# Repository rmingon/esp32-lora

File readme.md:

# ESP32 LoRa Nunchuck System

## Overview
This project integrates an ESP32 microcontroller with LoRa communication and two Nunchuck connectors, enabling remote control and data transmission applications. The system is designed for long-range communication while leveraging the Wii Nunchuck controllers for user input.

## Features
- **ESP32**: Wi-Fi and Bluetooth-enabled microcontroller
- **LoRa Module**: Long-range communication support
- **Dual Nunchuck Connectors on Separate I²C Buses**
- **Powered via USB**: No LiPo battery required

## Hardware Requirements
- ESP32 development board
- LoRa module (RFM95W-868S2)
- Two Wii Nunchuck controllers
- Nunchuck connectors
- USB power source
- Jumper wires & breadboard (or custom PCB)

## Wiring Diagram (Based on Schematic)
| ESP32 Pin | LoRa Pin | Nunchuck 1 Pin | Nunchuck 2 Pin |
|-----------|---------|---------------|---------------|
| 3.3V      | VCC     | VCC           | VCC           |
| GND       | GND     | GND           | GND           |
| GPIO5     | NSS     | -             | -             |
| GPIO18    | SCK     | -             | -             |
| GPIO19    | MISO    | -             | -             |
| GPIO23    | MOSI    | -             | -             |
| GPIO26    | DIO0    | -             | -             |
| GPIO21    | -       | SDA (I²C 1)   | -             |
| GPIO22    | -       | SCL (I²C 1)   | -             |
| GPIO25    | -       | -             | SDA (I²C 2)   |
| GPIO33    | -       | -             | SCL (I²C 2)   |

## Software Requirements
- Arduino IDE / PlatformIO
- ESP32 board package
- LoRa library (e.g., `RadioHead` or `LoRa.h`)
- Nunchuck library (e.g., `Wire.h`, `ArduinoNunchuk.h`)

## Usage
1. Connect the hardware components as per the wiring diagram.
2. Power up the ESP32 via USB.
3. Use the Nunchuck controllers to send data via LoRa.
4. Monitor data via serial output.

## Example Code
```cpp
#include <Wire.h>
#include <ArduinoNunchuk.h>
#include <LoRa.h>

TwoWire I2C_1 = TwoWire(0);
TwoWire I2C_2 = TwoWire(1);

ArduinoNunchuk nunchuk1;
ArduinoNunchuk nunchuk2;

void setup() {
    Serial.begin(115200);
    I2C_1.begin(21, 22); // SDA1 = GPIO21, SCL1 = GPIO22
    I2C_2.begin(25, 33); // SDA2 = GPIO25, SCL2 = GPIO33
    
    nunchuk1.init(I2C_1);
    nunchuk2.init(I2C_2);
    
    LoRa.begin(915E6);
}

void loop() {
    nunchuk1.update();
    nunchuk2.update();
    
    LoRa.beginPacket();
    LoRa.print(nunchuk1.analogX);
    LoRa.print(",");
    LoRa.print(nunchuk2.analogX);
    LoRa.endPacket();
    
    delay(100);
}
```

## Contributing
Feel free to submit issues or pull requests for improvements and bug fixes.

---
Happy coding! 🚀

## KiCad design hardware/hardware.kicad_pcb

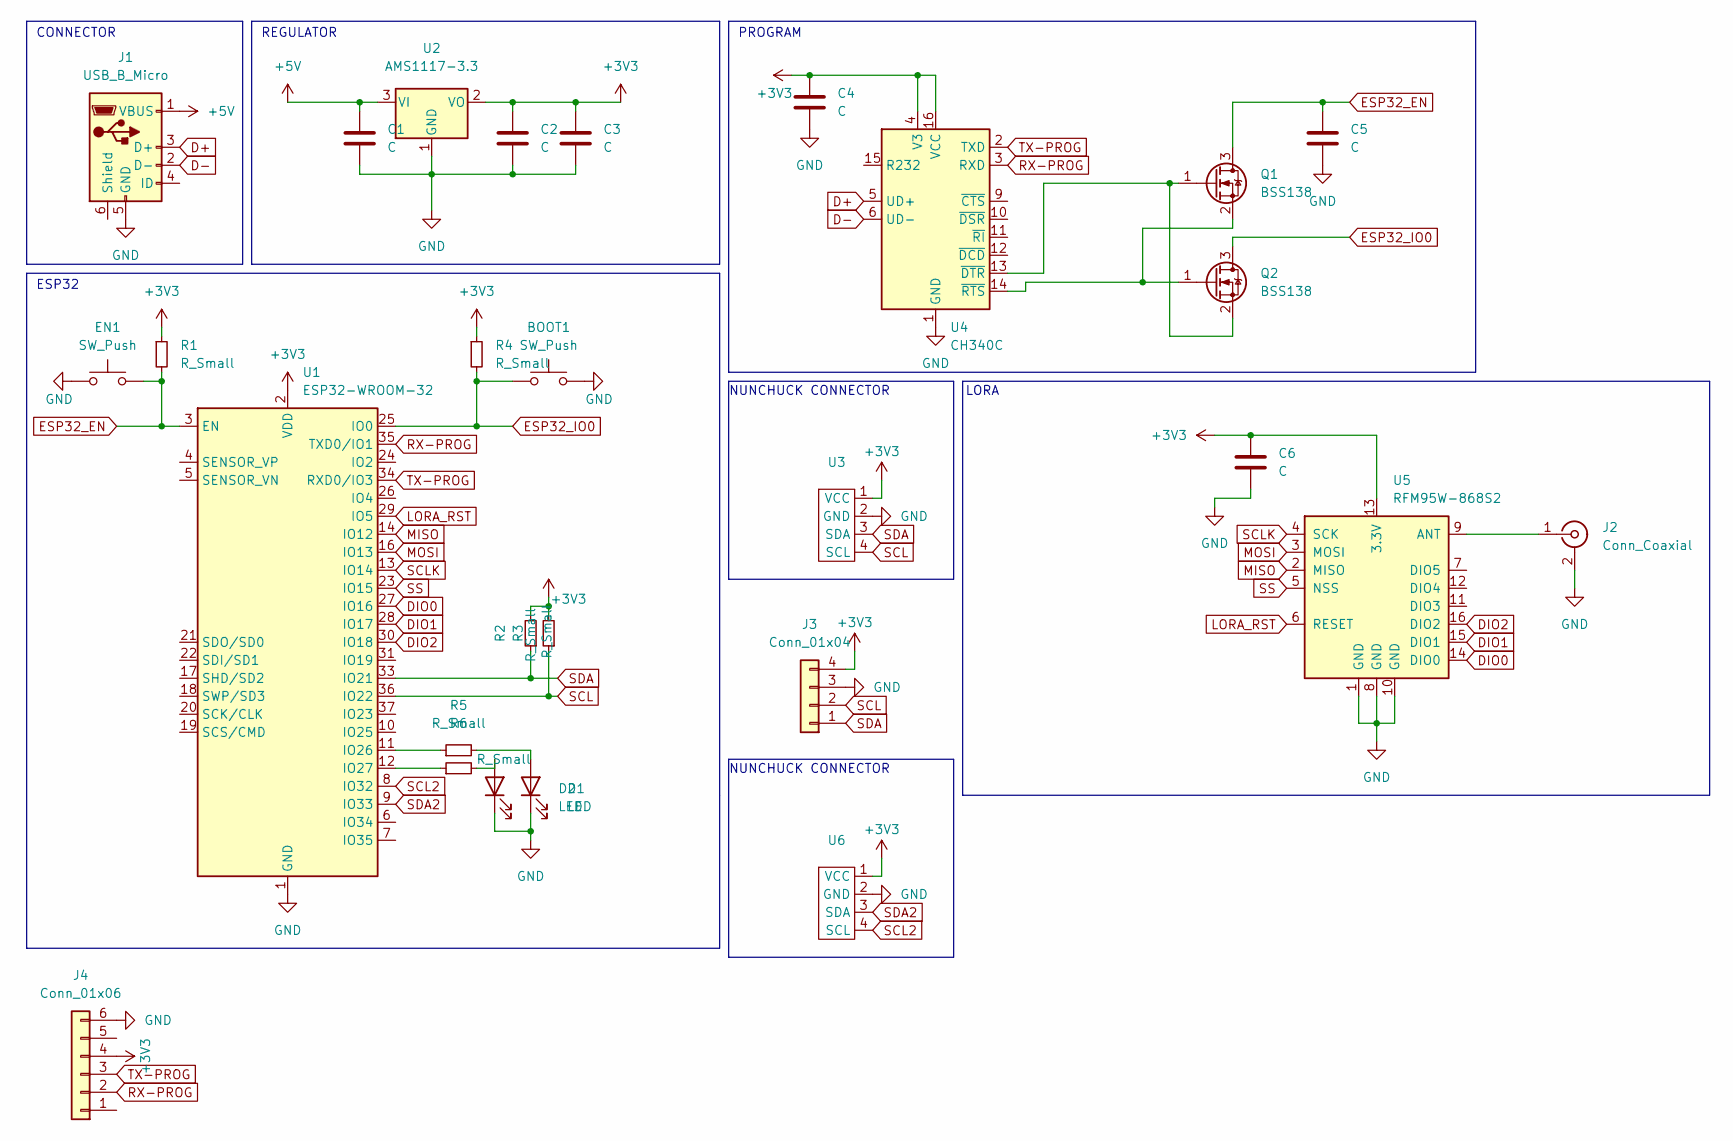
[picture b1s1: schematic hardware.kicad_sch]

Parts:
BOOT1: SW_Push; SW_SPST_FSMSM
C1, C2, C3, C4, C5, C6: C; C_0603_1608Metric
D1, D2: LED; LED_0603_1608Metric
EN1: SW_Push; SW_SPST_FSMSM
J1: USB_B_Micro; USB_Micro-B_Amphenol_10118194_Horizontal
J2: Conn_Coaxial; SMA_Samtec_SMA-J-P-H-ST-EM1_EdgeMount
J3: Conn_01x04; PinHeader_1x04_P2.54mm_Vertical
J4: Conn_01x06; PinHeader_1x06_P2.54mm_Vertical
Q1, Q2: BSS138; SOT-23
R1, R2, R3, R4, R5, R6: R_Small; R_0603_1608Metric
U1: ESP32-WROOM-32
U2: AMS1117-3.3; SOT-223-3_TabPin2
U3, U6: nunchuck
U4: CH340C; SOIC-16_3.9x9.9mm_P1.27mm
U5: RFM95W-868S2; HOPERF_RFM9XW_SMD

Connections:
+3V3: C2.1, C3.1, C4.1, C6.1, J3.4, J4.4, R1.1, R2.2, R3.2, R4.1, U1.2 (VDD), U2.2 (VO), U3.1 (VCC), U4.4 (V3), U4.16 (VCC), U5.13 (3.3V), U6.1 (VCC)
+5V: C1.1, J1.1 (VBUS), U2.3 (VI)
D+: J1.3 (D+), U4.5 (UD+)
D-: J1.2 (D-), U4.6 (UD-)
DIO0: U1.27 (IO16), U5.14 (DIO0)
DIO1: U1.28 (IO17), U5.15 (DIO1)
DIO2: U1.30 (IO18), U5.16 (DIO2)
ESP32_EN: C5.1, EN1.2, Q1.3 (D), R1.2, U1.3 (EN)
ESP32_IO0: BOOT1.1, Q2.3 (D), R4.2, U1.25 (IO0)
GND: BOOT1.2, C1.2, C2.2, C3.2, C4.2, C5.2, C6.2, D1.1 (K), D2.1 (K), EN1.1, J1.5 (GND), J2.2 (Ext), J3.3, J4.6, U1.1 (GND), U1.15 (GND), U1.38 (GND), U1.39 (GND), U2.1 (GND), U3.2 (GND), U4.1 (GND), U5.1 (GND), U5.8 (GND), U5.10 (GND), U6.2 (GND)
LORA_RST: U1.29 (IO5), U5.6 (RESET)
MISO: U1.14 (IO12), U5.2 (MISO)
MOSI: U1.16 (IO13), U5.3 (MOSI)
unnamed: D1.2 (A), R6.2
unnamed: D2.2 (A), R5.2
unnamed: J2.1 (In), U5.9 (ANT)
unnamed: Q1.1 (G), Q2.2 (S), U4.13 (~DTR)
unnamed: Q1.2 (S), Q2.1 (G), U4.14 (~RTS)
unnamed: R5.1, U1.11 (IO26)
unnamed: R6.1, U1.12 (IO27)
RX-PROG: J4.2, U1.35 (TXD0/IO1), U4.3 (RXD)
SCL: J3.2, R3.1, U1.36 (IO22), U3.4 (SCL)
SCL2: U1.8 (IO32), U6.4 (SCL)
SCLK: U1.13 (IO14), U5.4 (SCK)
SDA: J3.1, R2.1, U1.33 (IO21), U3.3 (SDA)
SDA2: U1.9 (IO33), U6.3 (SDA)
SS: U1.23 (IO15), U5.5 (NSS)
TX-PROG: J4.3, U1.34 (RXD0/IO3), U4.2 (TXD)

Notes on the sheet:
CONNECTOR
ESP32
PROGRAM
LORA
REGULATOR
NUNCHUCK CONNECTOR

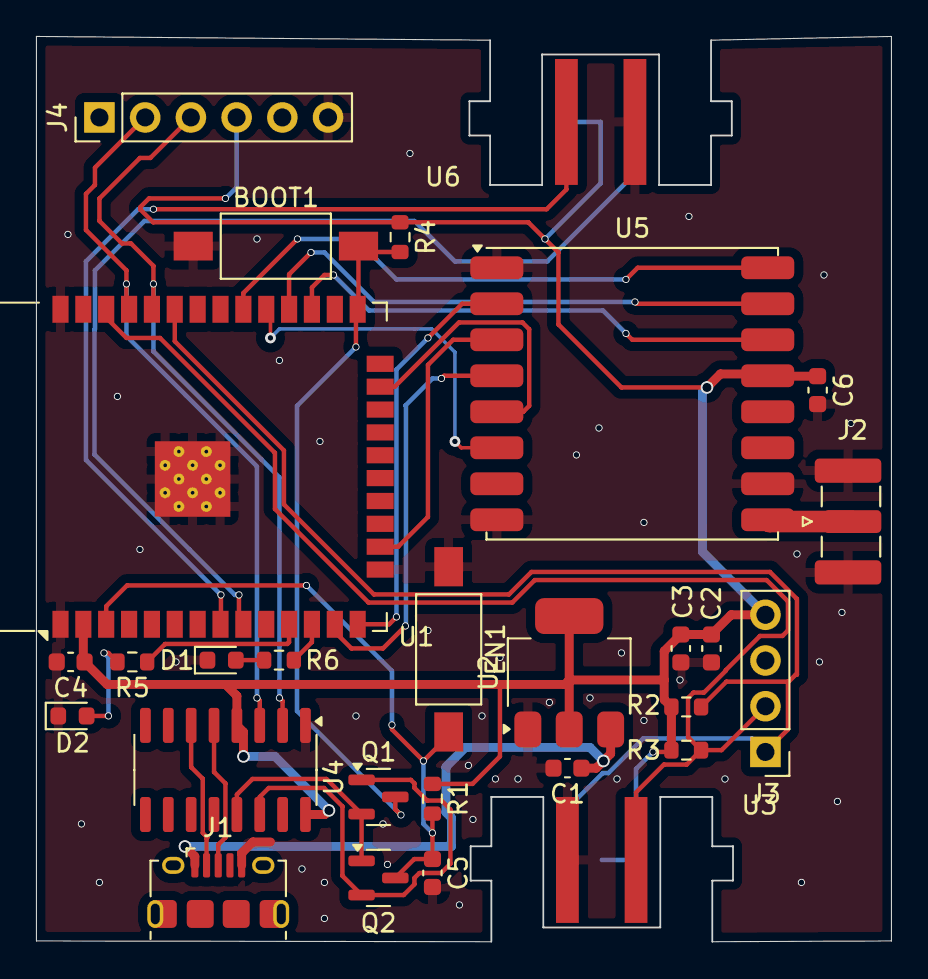
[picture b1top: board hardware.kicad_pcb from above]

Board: 2 copper layers, 47.5 x 50.3 mm, 28 parts (0 on the bottom side), 28 nets.

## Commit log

2025-03-18 add schematic components
2025-03-18 add nunchuck footprint
2025-03-18 place pcb components
2025-03-19 lora wiring + pcb wiring
2025-03-19 invert i2c screen wiring
2025-03-19 add picture
2025-03-19 add readme doc
2025-03-19 add second nunchuck connector and pcb wiring
2025-03-19 add ftdi pin and wiring to esp
2025-03-19 remove install procedure
2025-04-04 add real picture
2025-04-06 fix i2c wiring and lora rst
2025-04-06 add i2c screen and nunchuck move on screen
2025-04-08 add ws server
